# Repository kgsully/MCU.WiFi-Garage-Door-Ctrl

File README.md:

# WiFi Garage Door Controller
ESP32-WROOM Based WiFi enabled garage door controller design.

 Please refer to the README docx or PDF found in the documentation folder for further information.
 
 Schematics and drawings may be found within the documentation folder (dimensions are in mm). 
 
 3D design / printing models are located under the 'Enclosure' folder.

 Design updated for additional endpoint to allow for use with Apple Watch.

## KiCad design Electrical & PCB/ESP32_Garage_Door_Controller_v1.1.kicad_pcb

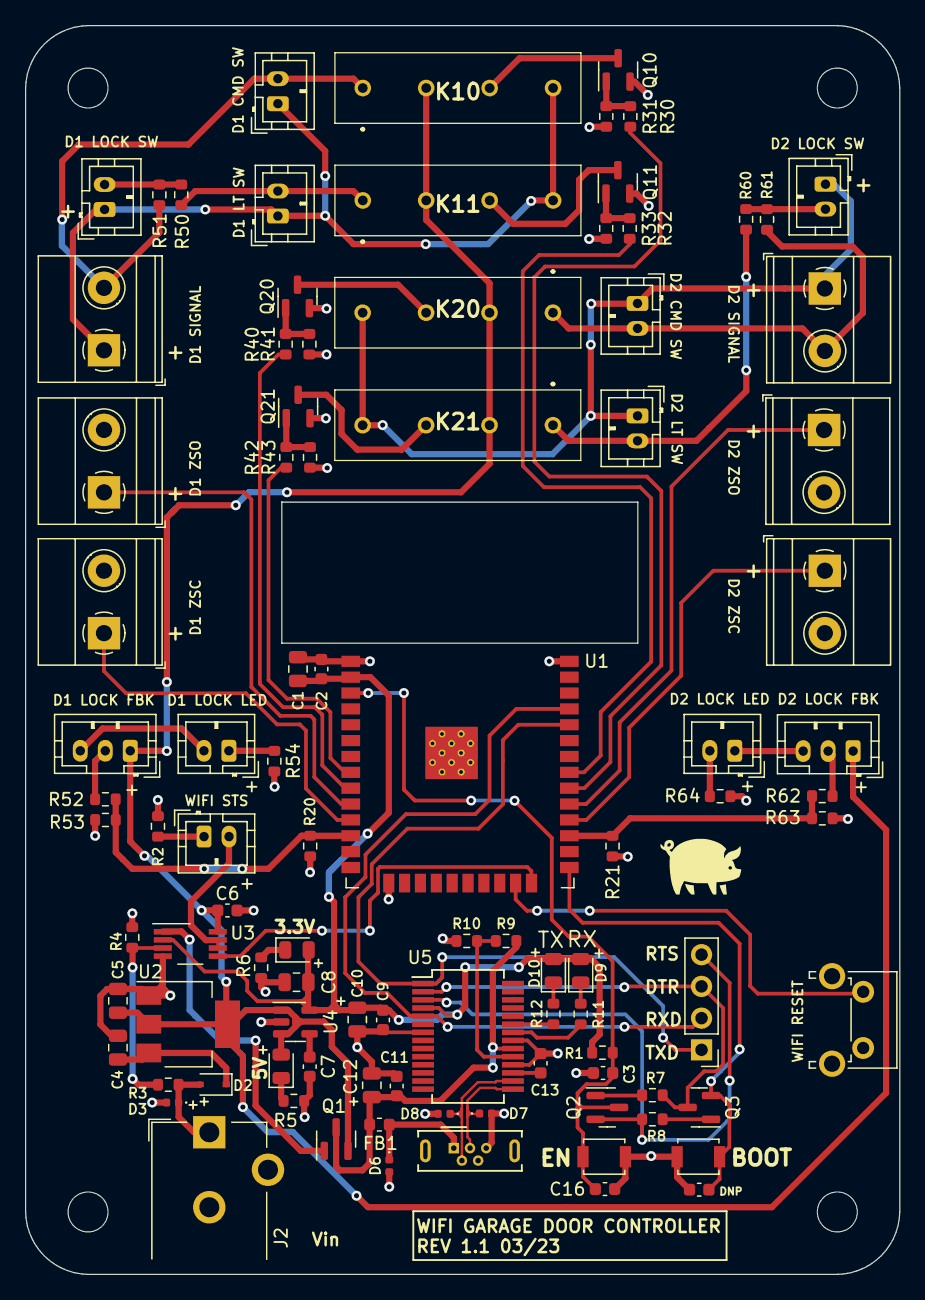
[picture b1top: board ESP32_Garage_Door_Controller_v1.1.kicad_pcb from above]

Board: 2 copper layers, 70.0 x 100.0 mm, 100 parts (0 on the bottom side), 64 nets.

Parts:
C1: 22u; C_0805_2012Metric
C2, C3, C9, C11, C16: 0.1u; C_0603_1608Metric
C4: 1u; C_0805_2012Metric
C5: 4u7; C_0805_2012Metric
C6: 100n; C_0603_1608Metric
C7: 10n; C_0603_1608Metric
C8: 2.2u; C_0805_2012Metric
C10, C12: 4.7u; C_0805_2012Metric
C13: 1u; C_0603_1608Metric
C14: 0u; C_0603_1608Metric
D2: BAT760,115; D_SOD-323
D3, D6, D7, D8: 5VWM; D_0402_1005Metric
D4: RED; LED_0805_2012Metric
D5, D9, D10: GRN; LED_0805_2012Metric
FB1: 40R; L_0603_1608Metric
H1, H2, H3, H4: MountingHole; MountingHole_3.2mm_M3
J1: Conn_01x04_Male; PinHeader_1x04_P2.54mm_Vertical
J2: 2.1mm; BarrelJack_CUI_PJ-102AH_Horizontal
J3: USB_B_Micro; USB_Micro-B_Wuerth_614105150721_Vertical
J10, J11, J12, J20, J21, J22, J31, J51, J61: Conn_01x02_Male; JST_PH_B2B-PH-K_1x02_P2.00mm_Vertical
J50, J60: Conn_01x03_Male; JST_PH_B3B-PH-K_1x03_P2.00mm_Vertical
J100, J101, J102, J200, J201, J202: 1935776; TerminalBlock_Phoenix_MKDS-1,5-2_1x02_P5.00mm_Horizontal
K10, K11, K20, K21: HE3621A0510
Q1: DMP2110U-7; SOT-23
Q2, Q3: SS8050-G; SOT-23
Q10, Q11, Q20, Q21: SI2302A-TP; SOT-23
R1, R3, R4, R7, R8, R10, R31, R33, R41, R43: 10k; R_0603_1608Metric
R2: 470R; R_0603_1608Metric
R5, R6, R11, R12, R30, R32, R40, R42, R52, R54, R62, R64: 1k; R_0603_1608Metric
R9, R20, R21: 4k7; R_0603_1608Metric
R50, R60: 121R; R_0603_1608Metric
R51, R61: 82r5; R_0603_1608Metric
R53, R63: 2k; R_0603_1608Metric
SW1, SW2: SW_Push; SW_SPST_B3U-1000P
SW30: SW_Push; SW_Tactile_SPST_Angled_PTS645Vx58-2LFS
U1: ESP32-WROOM-32D; ESP32-WROOM-32
U2: LDL1117S50R; SOT-223-3_TabPin2
U3: LMV358IDGKR; VSSOP-8_3.0x3.0mm_P0.65mm
U4: SPX3819M5-L-3-3; SOT-23-5
U5: CY7C65213-28PVXI; SSOP-28_5.3x10.2mm_P0.65mm

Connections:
+3.3V: C1.1, C2.1, C8.1, C9.2, C10.1, D5.2 (A), D9.2 (A), D10.2 (A), R1.1, U1.2 (VDD), U3.2 (-), U4.5 (OUT), U5.4 (VCCIO)
+5V: C5.1, C6.1, D4.2 (A), J50.1, J60.1, K10.2 (COIL_+), K11.2 (COIL_+), K20.2 (COIL_+), K21.2 (COIL_+), Q1.2 (S), U2.2 (VO), U3.8 (V+), U4.1 (IN), U4.3 (EN)
/ESP32 MCU/DTR: J1.3, Q3.3 (C), R7.1, U5.2 (DTR)
/ESP32 MCU/EN: C3.1, C16.2, Q2.3 (C), R1.2, SW2.2, U1.3 (EN)
/ESP32 MCU/IO0: C14.2, Q3.2 (E), SW1.2, U1.25 (IO0)
/ESP32 MCU/IO2: U1.24 (IO2), U3.5 (+)
/ESP32 MCU/IO5: J201.1, U1.29 (IO5)
/ESP32 MCU/IO16: R21.1, R62.1, R63.2, U1.27 (IO16)
/ESP32 MCU/IO17: J202.1, U1.28 (IO17)
/ESP32 MCU/IO18: R30.1, U1.30 (IO18)
/ESP32 MCU/IO19: R32.1, U1.31 (IO19)
/ESP32 MCU/IO25: J101.1, U1.10 (IO25)
/ESP32 MCU/IO26: J102.1, U1.11 (IO26)
/ESP32 MCU/IO27: R20.1, R52.1, R53.2, U1.12 (IO27)
/ESP32 MCU/IO32: R42.1, U1.8 (IO32)
/ESP32 MCU/IO33: R40.1, U1.9 (IO33)
/ESP32 MCU/RTS: J1.4, Q2.2 (E), R8.2, U5.3 (RTS)
/ESP32 MCU/RXD: J1.2, U1.35 (TXD0/IO1), U5.5 (RXD)
/ESP32 MCU/TXD: J1.1, U1.34 (RXD0/IO3), U5.1 (TXD)
/ESP32 MCU/WIFI_RES: SW30.1, U1.23 (IO15)
/Garage Door Circuits/D1_COM: J10.2, J100.2, K10.1 (NO), R51.1
/Garage Door Circuits/D1_SIG: J10.1, J11.1, J12.1, J100.1, K10.4 (COM), K11.4 (COM)
/Garage Door Circuits/D2_COM: J20.2, J200.2, K20.1 (NO), R61.1
/Garage Door Circuits/D2_SIG: J20.1, J21.1, J22.1, J200.1, K20.4 (COM), K21.4 (COM)
/Power Supply/VBUS: C11.2, C12.1, FB1.2, Q1.3 (D), R9.2, U5.20 (VCC)
/Power Supply/VIN: D2.2 (A), D3.1 (A1), J2.1, R3.1
/USB-UART Interface/USB_D+: D7.1 (A1), J3.3 (D+), U5.15 (USBDP)
/USB-UART Interface/USB_D-: D8.1 (A1), J3.2 (D-), U5.16 (USBDM)
GND: C1.2, C2.2, C3.2, C4.2, C5.2, C6.2, C7.2, C8.2, C9.1, C10.2, C11.1, C12.2, C13.2, C14.1, C16.1, D3.2 (A2), D6.2 (A2), D7.2 (A2), D8.2 (A2), J2.2, J3.5 (GND), J101.2, J102.2, J201.2, J202.2, Q10.2 (S), Q11.2 (S), Q20.2 (S), Q21.2 (S), R2.2, R4.2, R5.2, R6.2, R10.1, R20.2, R21.2, R31.2, R33.2, R41.2, R43.2, R53.1, R54.2, R63.1, R64.2, SW1.1, SW2.1, SW30.2, U1.1 (GND), U1.15 (GND), U1.38 (GND), U1.39 (GND), U2.1 (GND), U3.4 (V-), U4.2 (GND), U5.7 (GND), U5.18 (GND), U5.21 (GND)
unnamed: C4.1, D2.1 (K), U2.3 (VI)
unnamed: C7.1, U4.4 (BP)
unnamed: C13.1, U5.17 (VCCD)
unnamed: D4.1 (K), R5.1
unnamed: D5.1 (K), R6.1
unnamed: D6.1 (A1), FB1.1, J3.1 (VBUS)
unnamed: D9.1 (K), R11.2
unnamed: D10.1 (K), R12.2
unnamed: J11.2, K11.1 (NO), R50.2
unnamed: J12.2, R50.1, R51.2
unnamed: J21.2, K21.1 (NO), R60.2
unnamed: J22.2, R60.1, R61.2
unnamed: J31.1, R2.1
unnamed: J31.2, U3.6 (-), U3.7
unnamed: J50.2, R52.2
unnamed: J50.3, J51.2
unnamed: J51.1, R54.1
unnamed: J60.2, R62.2
unnamed: J60.3, J61.1
unnamed: J61.2, R64.1
unnamed: K10.3 (COIL_-), Q10.3 (D)
unnamed: K11.3 (COIL_-), Q11.3 (D)
unnamed: K20.3 (COIL_-), Q20.3 (D)
unnamed: K21.3 (COIL_-), Q21.3 (D)
unnamed: Q1.1 (G), U3.1
unnamed: Q2.1 (B), R7.2
unnamed: Q3.1 (B), R8.1
unnamed: Q10.1 (G), R30.2, R31.1
unnamed: Q11.1 (G), R32.2, R33.1
unnamed: Q20.1 (G), R40.2, R41.1
unnamed: Q21.1 (G), R42.2, R43.1
unnamed: R3.2, R4.1, U3.3 (+)
unnamed: R9.1, R10.2, U5.19 (~RESET)
unnamed: R11.1, U5.22 (GPIO1)
unnamed: R12.1, U5.23 (GPIO0)

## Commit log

2024-08-11 Refactored: separate JS from HTML / Updated: Added minimalistic website that doesn't use JS that is intended to be used via a smartwatch
2025-01-30 Update README.md
    Updated readme to add photos
2025-01-30 Update README.md
    Updated readme description
